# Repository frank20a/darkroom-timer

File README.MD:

# Darkroom f-stop timer

## Known issues:
- [X] Fix EPD power pin connected to 3.3V instead of 3V3 in KiCad schematic
- [ ] Fix SD card support (or remove it)
- [ ] Fix relays not working on PCB
- [ ] Fix issue with power supply voltage drop
    1. Test with a different power supply
    2. Add voltage measurement feedback to the microcontroller to monitor voltage levels

## Additions for future revisions:
- [ ] Add/Implement the following settings on the menu:
    - [ ] Ramp speed for light output changes
    - [ ] Save & Load templates
- [ ] Move EPD to a separate SPI bus to free up the main SPI bus for other peripherals
- [ ] Move EPD processing to a separate thread to improve responsiveness of the main application
- [ ] Add a safelight switch that bypasses everything
- [ ] Foot pedal support
- [ ] Add sensor support for light and contrast metering
- [ ] Add sensor support for color balancing

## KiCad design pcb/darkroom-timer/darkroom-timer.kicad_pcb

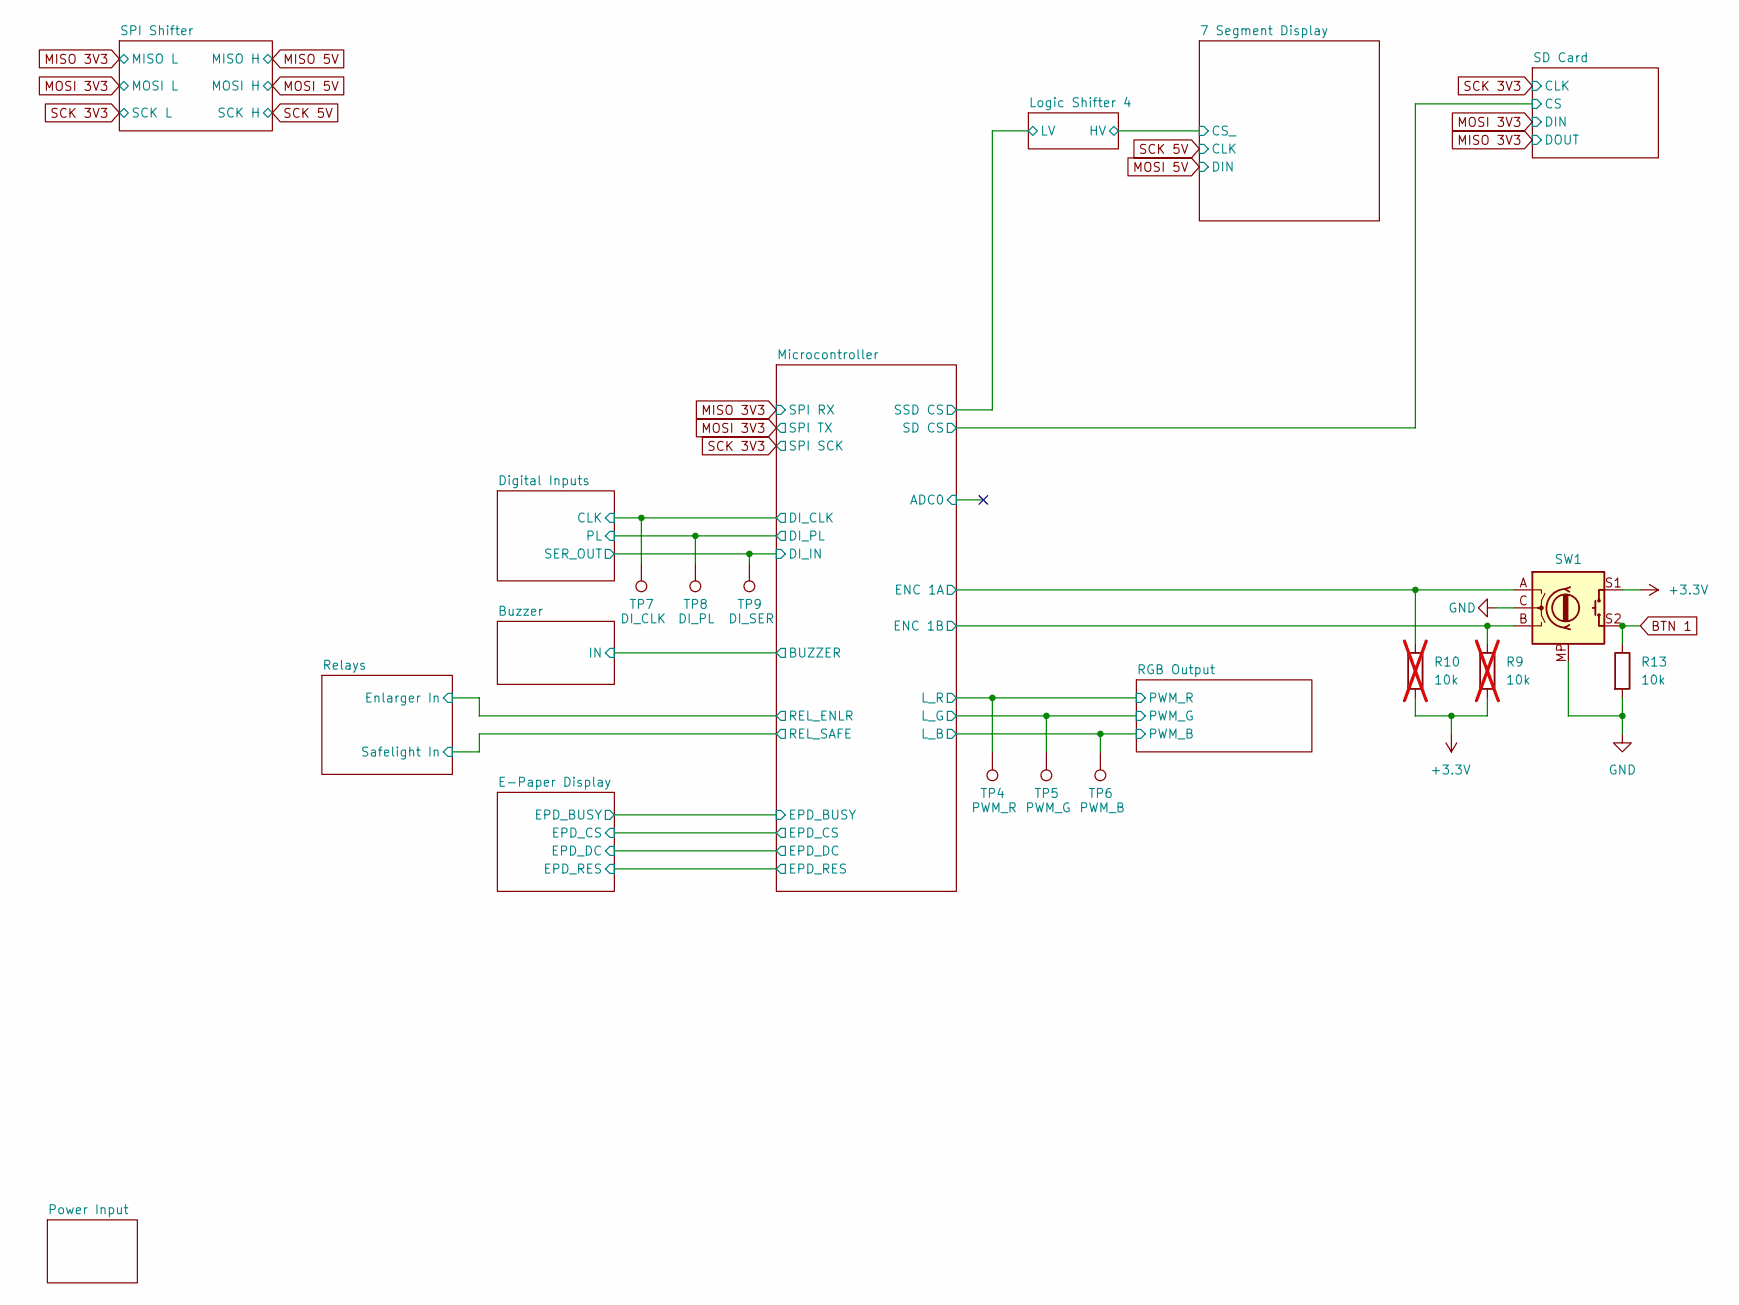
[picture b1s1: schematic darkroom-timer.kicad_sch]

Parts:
R9, R10: 10k; R_0805_2012Metric; not fitted
R13: 10k; R_0805_2012Metric
SW1: RotaryEncoder_Switch_MP; RotaryEncoder_Alps_EC11E-Switch_Vertical_3D
TP4: PWM_R; TestPoint_Pad_D1.5mm
TP5: PWM_G; TestPoint_Pad_D1.5mm
TP6: PWM_B; TestPoint_Pad_D1.5mm
TP7: DI_CLK; TestPoint_Pad_D1.5mm
TP8: DI_PL; TestPoint_Pad_D1.5mm
TP9: DI_SER; TestPoint_Pad_D1.5mm

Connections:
+3.3V: R9.2, R10.2, SW1.S1; also elsewhere on the board
/Digital Inputs/CLK: TP7.1; also elsewhere on the board
/Digital Inputs/PL: TP8.1; also elsewhere on the board
/Digital Inputs/SER_OUT: TP9.1; also elsewhere on the board
/Microcontroller/ENC 1A: R10.1, SW1.A; also elsewhere on the board
/Microcontroller/ENC 1B: R9.1, SW1.B; also elsewhere on the board
/Microcontroller/L_B: TP6.1; also elsewhere on the board
/Microcontroller/L_G: TP5.1; also elsewhere on the board
/Microcontroller/L_R: TP4.1; also elsewhere on the board
BTN 1: R13.1, SW1.S2; also elsewhere on the board
Earth: R13.2, SW1.C, SW1.MP; also elsewhere on the board

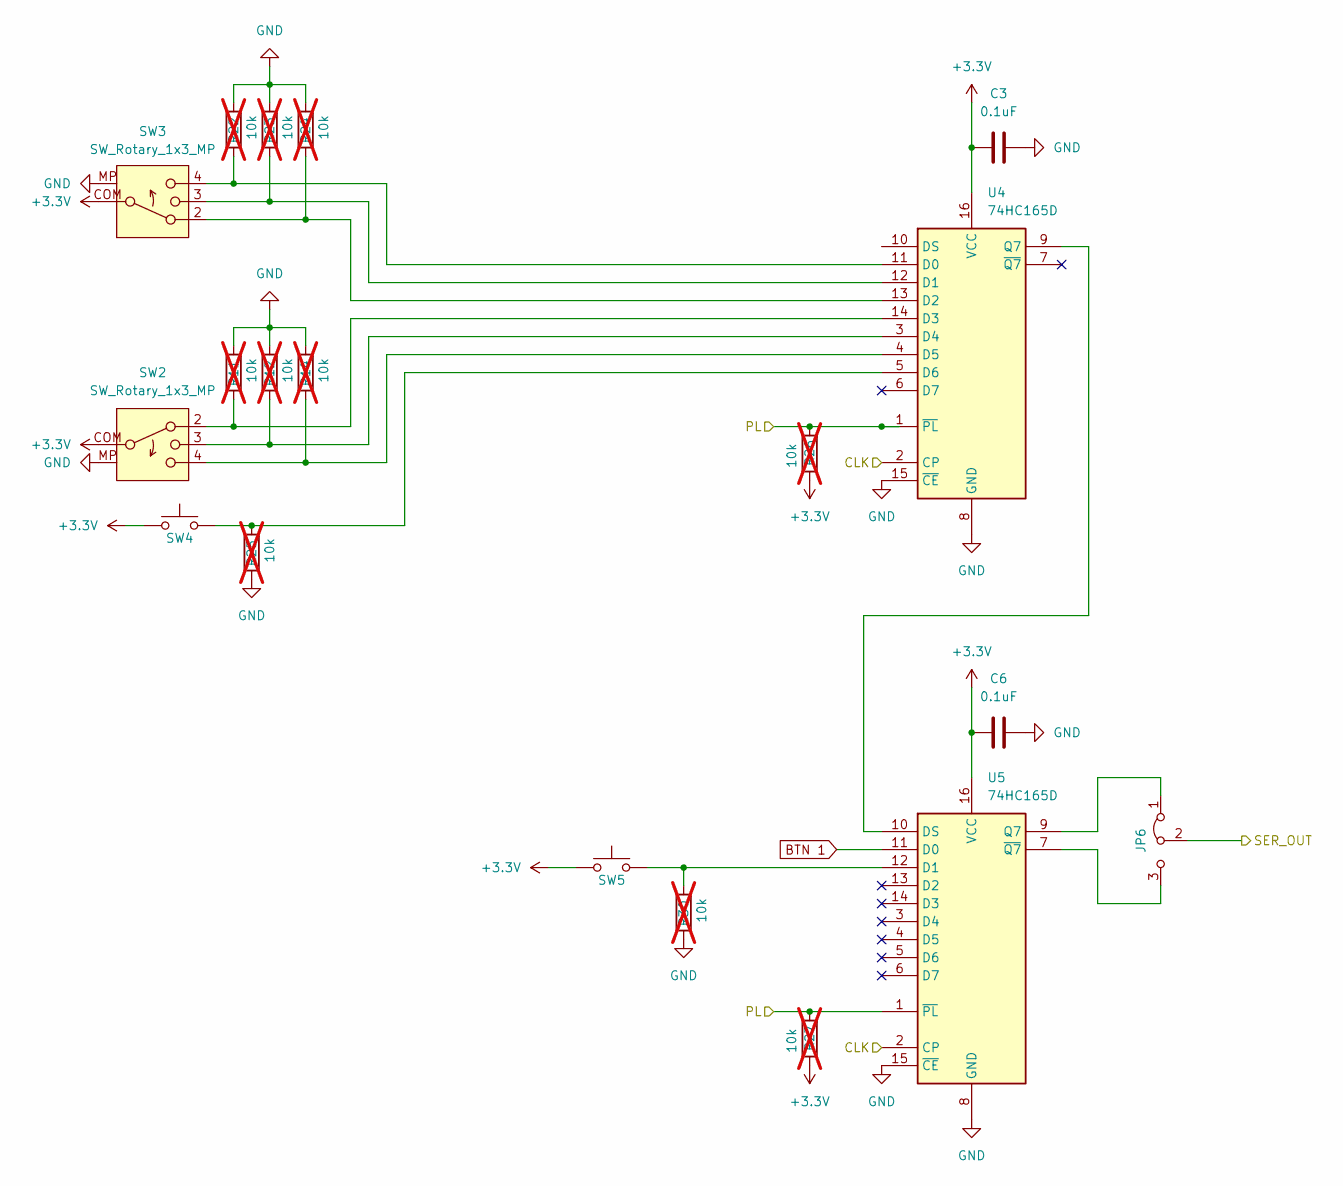
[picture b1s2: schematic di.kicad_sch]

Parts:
C3, C6: 0.1uF; C_0805_2012Metric
JP6: SolderJumper-3_P1.3mm_Bridged12_Pad1.0x1.5mm
R11, R12, R14, R22, R23, R24, R25, R26, R27, R30: 10k; R_0805_2012Metric; not fitted
SW2, SW3: SW_Rotary_1x3_MP; SR17A-007
SW4: Start Switch; SolderWire-0.25sqmm_1x02_P4.5mm_D0.65mm_OD2mm
SW5: Start Switch; SW_PUSH_6mm_H13mm
U4, U5: 74HC165D; SO-16_3.9x9.9mm_P1.27mm

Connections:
+3.3V: C3.1, C6.1, R26.1, R27.1, SW2.COM, SW3.COM, SW4.1, SW5.1, U4.16 (VCC), U5.16 (VCC); also elsewhere on the board
/Digital Inputs/CLK: U4.2 (CP), U5.2 (CP); also elsewhere on the board
/Digital Inputs/PL: R26.2, R27.2, U4.1 (~PL), U5.1 (~PL); also elsewhere on the board
/Digital Inputs/SER_OUT: JP6.2 (C); also elsewhere on the board
BTN 1: U5.11 (D0); also elsewhere on the board
Earth: C3.2, C6.2, R11.1, R12.1, R14.1, R22.1, R23.1, R24.1, R25.2, R30.2, SW2.MP, SW3.MP, U4.8 (GND), U4.15 (~CE), U5.8 (GND), U5.15 (~CE); also elsewhere on the board
unnamed: JP6.1 (A), U5.9 (Q7)
unnamed: JP6.3 (B), U5.7 (~Q7)
unnamed: R22.2, SW3.4, U4.11 (D0)
unnamed: R23.2, SW3.3, U4.12 (D1)
unnamed: R24.2, SW3.2, U4.13 (D2)
unnamed: R11.2, SW2.2, U4.14 (D3)
unnamed: R12.2, SW2.3, U4.3 (D4)
unnamed: R14.2, SW2.4, U4.4 (D5)
unnamed: R25.1, SW4.2, U4.5 (D6)
unnamed: U4.9 (Q7), U5.10 (DS)
unnamed: R30.1, SW5.2, U5.12 (D1)

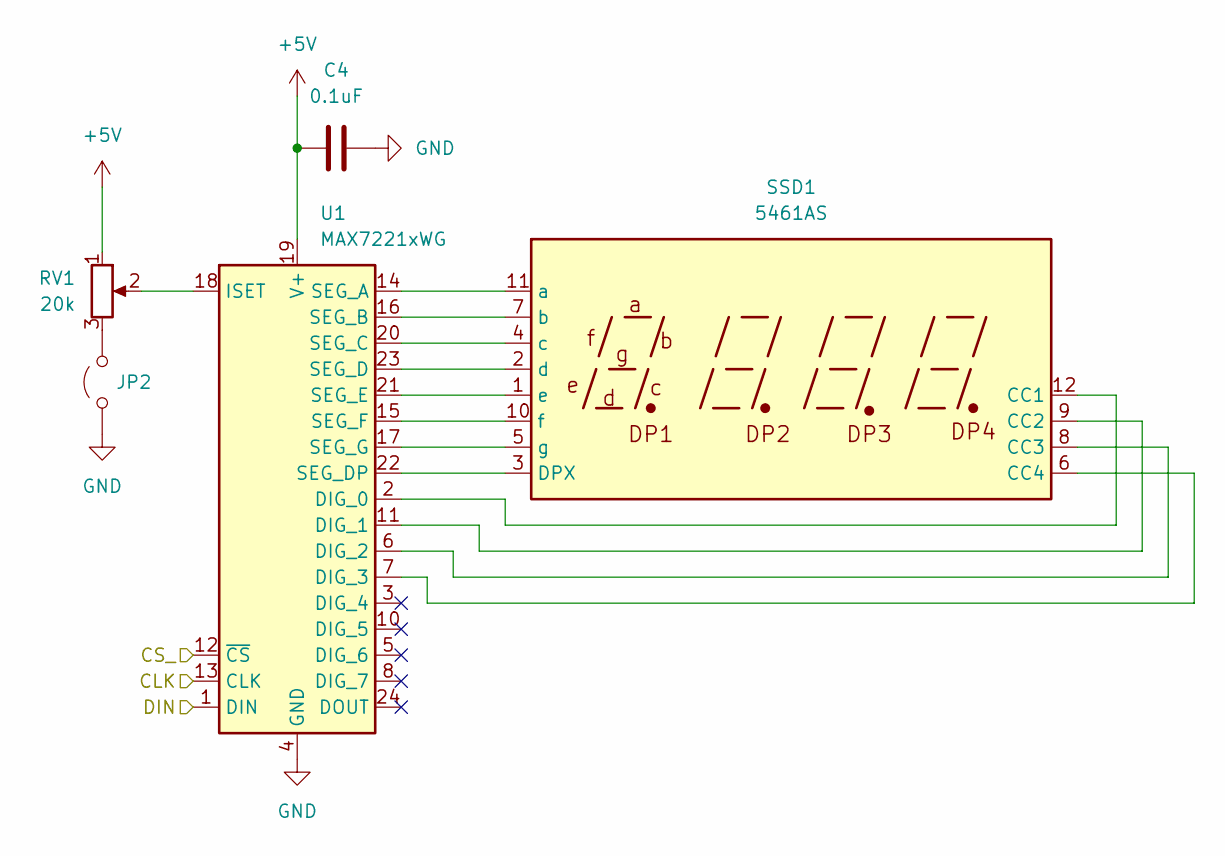
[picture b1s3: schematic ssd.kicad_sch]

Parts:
C4: 0.1uF; C_0805_2012Metric
JP2: SolderJumper-2_P1.3mm_Open_Pad1.0x1.5mm
RV1: 20k; RKT6V
SSD1: 5461AS; CA56-12EWA
U1: MAX7221xWG; SOIC-24W_7.5x15.4mm_P1.27mm

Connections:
+5V: C4.1, RV1.1, U1.19 (V+); also elsewhere on the board
/7 Segment Display/CS_: U1.12 (~CS); also elsewhere on the board
Earth: C4.2, JP2.1 (A), U1.4 (GND), U1.9 (GND); also elsewhere on the board
MOSI 5V: U1.1 (DIN); also elsewhere on the board
unnamed: JP2.2 (B), RV1.3
unnamed: SSD1.12 (CC1), U1.2 (DIG_0)
unnamed: SSD1.9 (CC2), U1.11 (DIG_1)
unnamed: SSD1.8 (CC3), U1.6 (DIG_2)
unnamed: SSD1.6 (CC4), U1.7 (DIG_3)
unnamed: SSD1.3 (DPX), U1.22 (SEG_DP)
unnamed: SSD1.11 (a), U1.14 (SEG_A)
unnamed: SSD1.7 (b), U1.16 (SEG_B)
unnamed: SSD1.4 (c), U1.20 (SEG_C)
unnamed: SSD1.2 (d), U1.23 (SEG_D)
unnamed: SSD1.1 (e), U1.21 (SEG_E)
unnamed: SSD1.10 (f), U1.15 (SEG_F)
unnamed: SSD1.5 (g), U1.17 (SEG_G)
unnamed: RV1.2, U1.18 (ISET)
SCK 5V: U1.13 (CLK); also elsewhere on the board

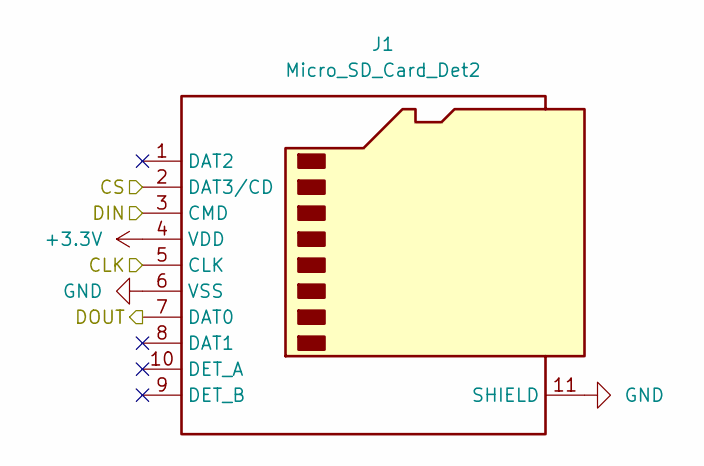
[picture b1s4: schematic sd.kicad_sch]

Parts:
J1: Micro_SD_Card_Det2; microSD_HC_Hirose_DM3AT-SF-PEJM5

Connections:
+3.3V: J1.4 (VDD); also elsewhere on the board
/Microcontroller/SD CS: J1.2 (DAT3/CD); also elsewhere on the board
Earth: J1.6 (VSS), J1.11 (SHIELD); also elsewhere on the board
MISO 3V3: J1.7 (DAT0); also elsewhere on the board
MOSI 3V3: J1.3 (CMD); also elsewhere on the board
SCK 3V3: J1.5 (CLK); also elsewhere on the board

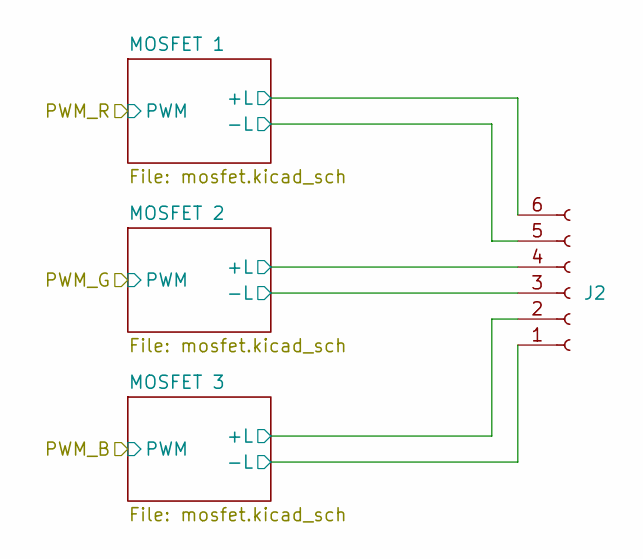
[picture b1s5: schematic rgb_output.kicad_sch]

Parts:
J2: Conn_01x06_Socket; PhoenixContact_MC_1,5_6-G-3.81_1x06_P3.81mm_Horizontal

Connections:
+24V: J2.2, J2.4, J2.6; also elsewhere on the board
/RGB Output/MOSFET 1/PWR_NEG: J2.5; also elsewhere on the board
/RGB Output/MOSFET 2/PWR_NEG: J2.3; also elsewhere on the board
/RGB Output/MOSFET 3/PWR_NEG: J2.1; also elsewhere on the board

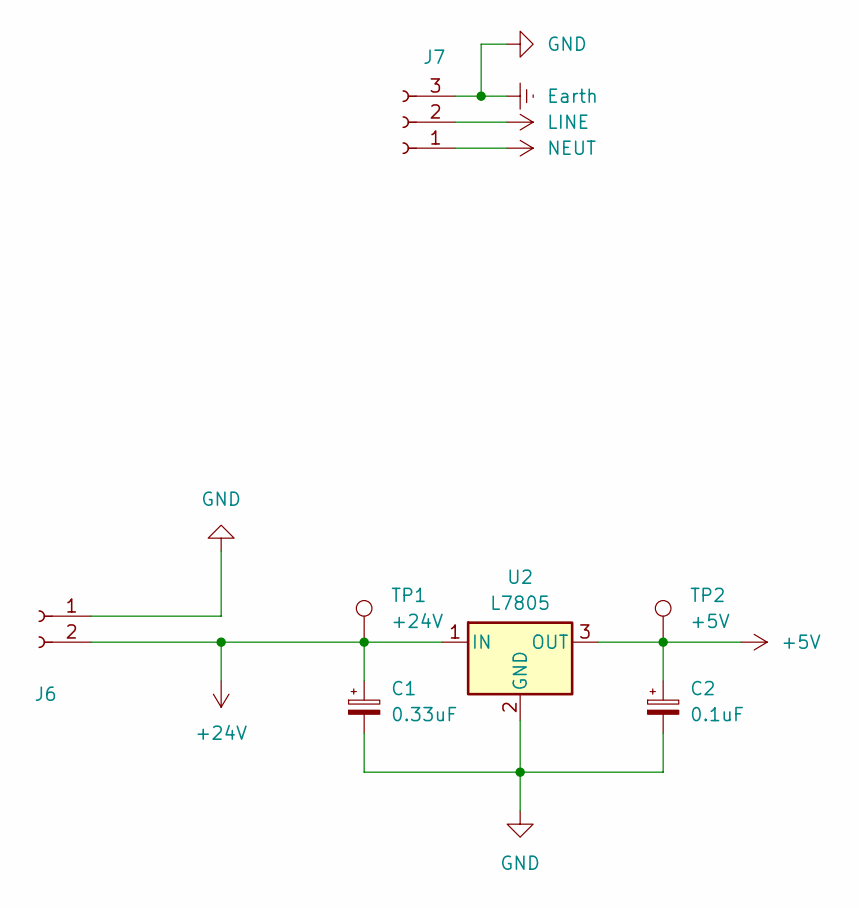
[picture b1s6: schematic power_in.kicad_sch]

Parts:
C1: 0.33uF; C_Radial_D4.0mm_H7.0mm_P1.50mm
C2: 0.1uF; C_Radial_D4.0mm_H7.0mm_P1.50mm
J6: Conn_01x02_Socket; PhoenixContact_MC_1,5_2-G-3.81_1x02_P3.81mm_Horizontal
J7: Conn_01x03_Socket; TerminalBlock_Phoenix_MKDS-1,5-3_1x03_P5.00mm_Horizontal
TP1: +24V; TestPoint_Pad_D1.5mm
TP2: +5V; TestPoint_Pad_D1.5mm
U2: L7805; TO-220-3_Vertical

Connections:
+5V: C2.1, TP2.1, U2.3 (OUT); also elsewhere on the board
+24V: C1.1, J6.2, TP1.1, U2.1 (IN); also elsewhere on the board
Earth: C1.2, C2.2, J6.1, J7.3, U2.2 (GND); also elsewhere on the board
LINE: J7.2; also elsewhere on the board
NEUT: J7.1; also elsewhere on the board

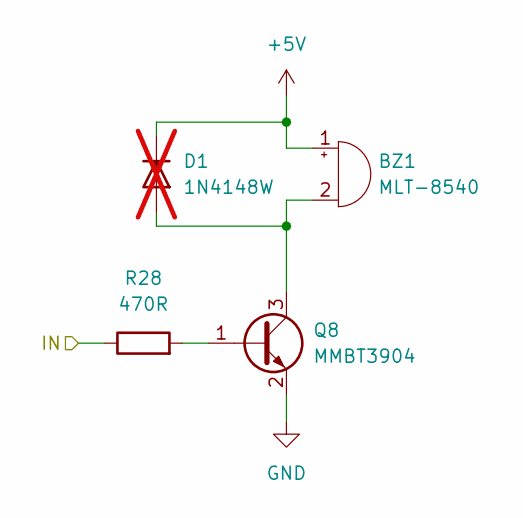
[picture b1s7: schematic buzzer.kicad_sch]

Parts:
BZ1: MLT-8540; Buzzer_MLT_8540
D1: 1N4148W; D_SOD-123; not fitted
Q8: MMBT3904; TSOT-23_HandSoldering
R28: 470R; R_0805_2012Metric

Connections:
+5V: BZ1.1 (+), D1.1 (K); also elsewhere on the board
/Buzzer/IN: R28.1; also elsewhere on the board
Earth: Q8.2 (E); also elsewhere on the board
unnamed: BZ1.2 (-), D1.2 (A), Q8.3 (C)
unnamed: Q8.1 (B), R28.2

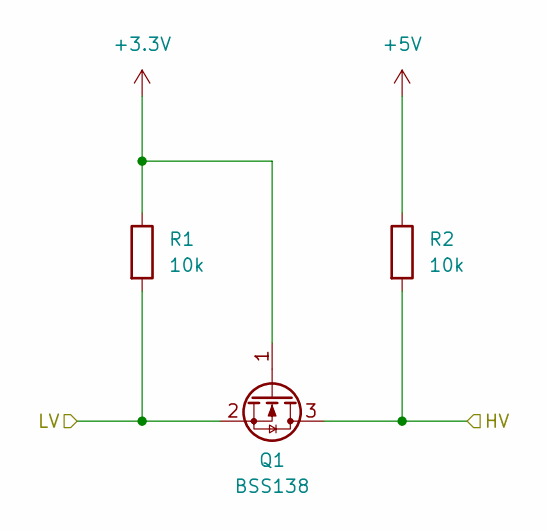
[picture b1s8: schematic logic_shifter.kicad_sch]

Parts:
Q1: BSS138; SOT-23
R1, R2: 10k; R_0805_2012Metric

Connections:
+3.3V: Q1.1 (G), R1.1; also elsewhere on the board
+5V: R2.1; also elsewhere on the board
MOSI 3V3: Q1.2 (S), R1.2; also elsewhere on the board
MOSI 5V: Q1.3 (D), R2.2; also elsewhere on the board

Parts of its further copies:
Q2, Q3, Q4: BSS138; SOT-23
R3, R4, R5, R6, R7, R8: 10k; R_0805_2012Metric

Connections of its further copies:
+3.3V: Q2.1 (G), Q3.1 (G), Q4.1 (G), R3.1, R5.1, R7.1; also elsewhere on the board
+5V: R4.1, R6.1, R8.1; also elsewhere on the board
/7 Segment Display/CS_: Q4.3 (D), R8.2; also elsewhere on the board
/Logic Shifter 4/LV: Q4.2 (S), R7.2; also elsewhere on the board
MISO 3V3: Q2.2 (S), R3.2; also elsewhere on the board
MISO 5V: Q2.3 (D), R4.2
SCK 3V3: Q3.2 (S), R5.2; also elsewhere on the board
SCK 5V: Q3.3 (D), R6.2; also elsewhere on the board

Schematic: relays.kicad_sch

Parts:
JP4: SolderJumper-3_P1.3mm_Bridged12_Pad1.0x1.5mm

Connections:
+5V: JP4.1 (A); also elsewhere on the board
+24V: JP4.3 (B); also elsewhere on the board
/Relays/Relay Enlarger/PWR_IN: JP4.2 (C); also elsewhere on the board

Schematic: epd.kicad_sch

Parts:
C5: 0.1uF; C_0805_2012Metric
J4: EPD Connector; PinHeader_2x04_P2.54mm_Vertical

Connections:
+3.3V: C5.1, J4.8; also elsewhere on the board
/E-Paper Display/EPD_BUSY: J4.1; also elsewhere on the board
/E-Paper Display/EPD_CS: J4.4; also elsewhere on the board
/E-Paper Display/EPD_D/C: J4.3; also elsewhere on the board
/E-Paper Display/EPD_RES: J4.2; also elsewhere on the board
Earth: C5.2, J4.7; also elsewhere on the board
MOSI 3V3: J4.5; also elsewhere on the board
SCK 3V3: J4.6; also elsewhere on the board

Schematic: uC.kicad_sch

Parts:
A1: RP Pico 2; RaspberryPi_Pico_SMD_HandSolder
JP1: SolderJumper-2_P1.3mm_Bridged_Pad1.0x1.5mm
JP3: SolderJumper-2_P1.3mm_Open_Pad1.0x1.5mm
TP3: +3V3; TestPoint_Pad_D1.5mm

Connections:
+3.3V: JP1.2 (B), JP3.1 (A), TP3.1; also elsewhere on the board
+5V: A1.40 (VBUS); also elsewhere on the board
/Buzzer/IN: A1.29 (GPIO22); also elsewhere on the board
/Digital Inputs/CLK: A1.12 (GPIO9); also elsewhere on the board
/Digital Inputs/PL: A1.14 (GPIO10); also elsewhere on the board
/Digital Inputs/SER_OUT: A1.15 (GPIO11); also elsewhere on the board
/E-Paper Display/EPD_BUSY: A1.16 (GPIO12); also elsewhere on the board
/E-Paper Display/EPD_CS: A1.17 (GPIO13); also elsewhere on the board
/E-Paper Display/EPD_D/C: A1.19 (GPIO14); also elsewhere on the board
/E-Paper Display/EPD_RES: A1.20 (GPIO15); also elsewhere on the board
/Logic Shifter 4/LV: A1.26 (GPIO20); also elsewhere on the board
/Microcontroller/ADC0: A1.31 (GPIO26_ADC0)
/Microcontroller/ENC 1A: A1.4 (GPIO2); also elsewhere on the board
/Microcontroller/ENC 1B: A1.5 (GPIO3); also elsewhere on the board
/Microcontroller/L_B: A1.9 (GPIO6); also elsewhere on the board
/Microcontroller/L_G: A1.7 (GPIO5); also elsewhere on the board
/Microcontroller/L_R: A1.6 (GPIO4); also elsewhere on the board
/Microcontroller/REL_ENLR: A1.11 (GPIO8); also elsewhere on the board
/Microcontroller/REL_SAFE: A1.10 (GPIO7); also elsewhere on the board
/Microcontroller/SD CS: A1.27 (GPIO21); also elsewhere on the board
Earth: A1.3 (GND), A1.8 (GND), A1.13 (GND), A1.18 (GND), A1.23 (GND), A1.28 (GND), A1.33 (AGND), A1.38 (GND); also elsewhere on the board
MISO 3V3: A1.21 (GPIO16); also elsewhere on the board
MOSI 3V3: A1.25 (GPIO19); also elsewhere on the board
unnamed: A1.36 (3V3), JP1.1 (A)
unnamed: A1.37 (3V3_EN), JP3.2 (B)
SCK 3V3: A1.24 (GPIO18); also elsewhere on the board

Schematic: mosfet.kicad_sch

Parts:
Q5: IRLB8721PBF; TO-220-3_Vertical
R15: 10k; R_0805_2012Metric
R16: 220R; R_0805_2012Metric

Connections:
/Microcontroller/L_R: R15.1, R16.1; also elsewhere on the board
/RGB Output/MOSFET 1/PWR_NEG: Q5.2 (D); also elsewhere on the board
Earth: Q5.3 (S), R15.2; also elsewhere on the board
unnamed: Q5.1 (G), R16.2

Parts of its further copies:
Q6, Q7: IRLB8721PBF; TO-220-3_Vertical
R17, R19: 10k; R_0805_2012Metric
R18, R20: 220R; R_0805_2012Metric

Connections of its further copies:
/Microcontroller/L_B: R19.1, R20.1; also elsewhere on the board
/Microcontroller/L_G: R17.1, R18.1; also elsewhere on the board
/RGB Output/MOSFET 2/PWR_NEG: Q6.2 (D); also elsewhere on the board
/RGB Output/MOSFET 3/PWR_NEG: Q7.2 (D); also elsewhere on the board
Earth: Q6.3 (S), Q7.3 (S), R17.2, R19.2; also elsewhere on the board
unnamed: Q6.1 (G), R18.2
unnamed: Q7.1 (G), R20.2

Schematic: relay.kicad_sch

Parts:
J3: Conn_01x02_Socket; TerminalBlock_Phoenix_MKDS-1,5-2_1x02_P5.00mm_Horizontal
K1: Relay_DPDT; Relay_DPDT_Panasonic_JW2_Custom
R21: 1k; R_0805_2012Metric
U3: PC817; DIP-4_W7.62mm

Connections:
/Microcontroller/REL_ENLR: U3.1; also elsewhere on the board
/Relays/Relay Enlarger/L_OUT: J3.1, K1.21
/Relays/Relay Enlarger/N_OUT: J3.2, K1.11
/Relays/Relay Enlarger/PWR_IN: R21.1; also elsewhere on the board
Earth: K1.A2, U3.2; also elsewhere on the board
LINE: K1.24; also elsewhere on the board
NEUT: K1.14; also elsewhere on the board
unnamed: K1.A1, U3.3
unnamed: R21.2, U3.4

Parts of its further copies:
J5: Conn_01x02_Socket; TerminalBlock_Phoenix_MKDS-1,5-2_1x02_P5.00mm_Horizontal
K2: Relay_DPDT; Relay_DPDT_Panasonic_JW2_Custom
R29: 1k; R_0805_2012Metric
U6: PC817; DIP-4_W7.62mm

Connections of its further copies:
/Microcontroller/REL_SAFE: U6.1; also elsewhere on the board
/Relays/Relay Enlarger/PWR_IN: R29.1; also elsewhere on the board
/Relays/Relay Safelight/L_OUT: J5.1, K2.21
/Relays/Relay Safelight/N_OUT: J5.2, K2.11
Earth: K2.A2, U6.2; also elsewhere on the board
LINE: K2.24; also elsewhere on the board
NEUT: K2.14; also elsewhere on the board
unnamed: K2.A1, U6.3
unnamed: R29.2, U6.4

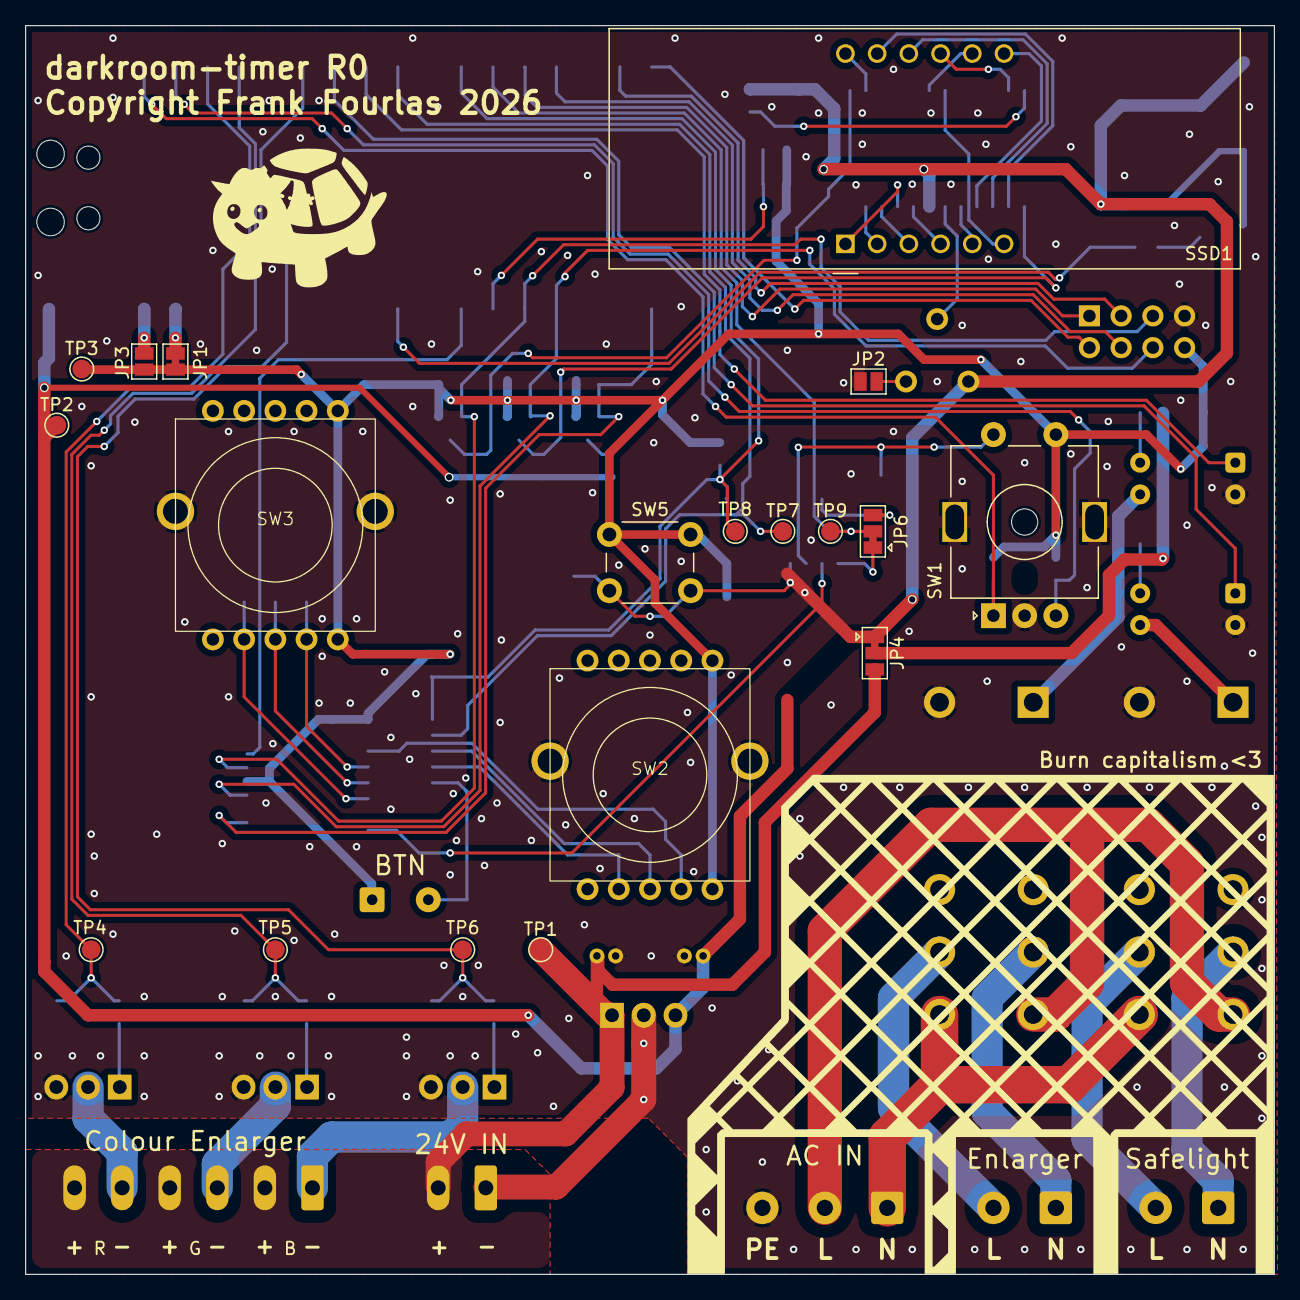
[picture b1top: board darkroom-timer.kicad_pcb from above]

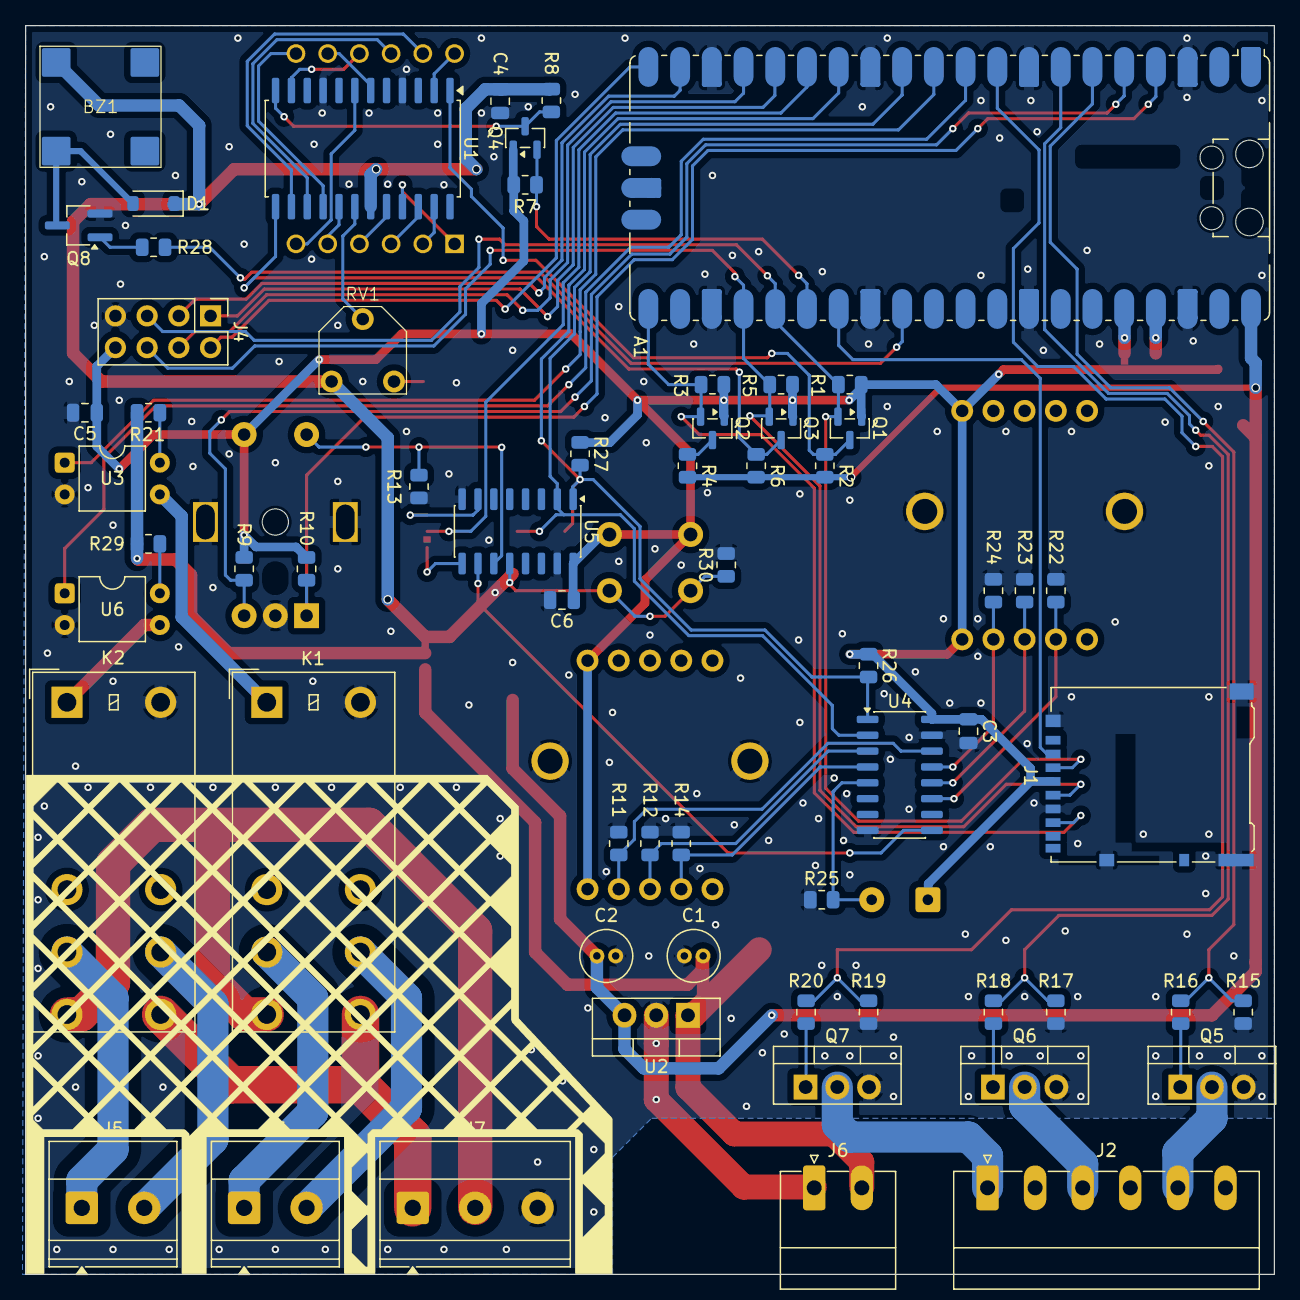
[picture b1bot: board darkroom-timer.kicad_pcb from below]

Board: 2 copper layers, 100.0 x 100.0 mm, 83 parts (63 on the bottom side), 75 nets.

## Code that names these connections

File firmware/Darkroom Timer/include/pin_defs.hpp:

#define MOSI_PIN 19
#define MISO_PIN 16
#define SCK_PIN 18

#define EPD_CS_PIN 13
#define EPD_DC_PIN 14
#define EPD_RES_PIN 15
#define EPD_BUSY_PIN 12

#define DI_IN_PIN 11
#define DI_PL_PIN 10
#define DI_CLK_PIN 9

#define REL_ENLR_PIN 8
#define REL_SAFE_PIN 7

#define LIGHT_OUT_R_PIN 4
#define LIGHT_OUT_G_PIN 5
#define LIGHT_OUT_B_PIN 6

#define BUZZER_PIN 22

#define ENC1_A_PIN 2
#define ENC1_B_PIN 3     // Assume that it is ENC1_A_PIN + 1

#define SSD_CS_PIN 20
#define SD_CS_PIN 21

// #define POT1_PIN A0

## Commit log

2026-03-09 PCB Schematic
2026-03-15 PCB Ready
2026-03-17 Correct Connectors
2026-03-21 Platform.IO Project Init
2026-03-23 EPD Tests
2026-03-27 Refactoring
2026-03-31 Encoder + Digital Inputs
2026-04-16 Shift Registers + Encoder + 7SD
2026-04-19 7SD decimal points
2026-04-19 SD Card Working
2026-04-19 Final PCB R0 design
2026-04-27 Settings page Major work + changes
2026-05-04 Settings menu fully operational Not all options finished
2026-05-09 Timer & Light Control Pages Done
2026-05-11 Test Strip Page
2026-05-12 Fix inrush current issue
2026-05-12 Readme update

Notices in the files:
pcb/darkroom-timer/darkroom-timer.kicad_pcb:
Copyright Frank Fourlas 2026
